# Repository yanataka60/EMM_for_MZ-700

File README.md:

# EMMボード for MZ-700

　MZ-700、MZ-80K、MZ-80C、MZ-1200、MZ-1500用の512K S-RAM EMMボードを作ってみました。

　EMMが対応しているHuBASICはMZ-700用だけです。MZ-80K用、MZ-1500用HuBASICはEMMに対応していないので外部記憶装置として使うためにはI/Oポートを直接制御して読み書きする必要があります。

　特徴としては、

　1)I/Oポートは、I・Oデータ機器 PIO-3034互換なのでそのままPIO-3034(320K EMM)として使えます。

　2)CR-2032のバックアップにより電源を切ってもメモリ内容が保持されます。(Rev1.5のバックアップ期間は計算上数年は大丈夫です。)

　3)スイッチにより書込み禁止にできます。

　4)I/Oポートから直接EMMを読み書きすれば512K外部RAMとして使えます。

　5)MZ-700_SD、MZ-80K_SD、MZ-1500_SDと併用すれば512KまるごとSDカードからLOAD、SAVEが可能です。

　6)ジャンパによりEMM0～EMM3のいずれかに設定して使えます。

　7)おまけでアドレスカウンタリセットを付けました。

#### 注)　出来ればMZ-700本体内から5Vを取り出し、EMMボードに供給してください。

#### 　　 電源アダプタを接続しての外部電源で使用する場合には次の順序で電源の入り切りを行わないとバックアップが正常に行われません。ただし、S4スイッチがROM側になっていれば電源入り切りの順番に影響されません。

#### 　　 1)電源を入れるときにはEMMボードより先にMZ-700本体の電源を入れる。

#### 　　 2)電源を切るときには先にEMMボードの電源を切ってからMZ-700本体の電源を切る。

　なお、MZ-700、MZ-80K、MZ-1500本体の通常の電源ON/OFFでの正常動作は確認していますが、電源ON/OFFを瞬間的に繰り返すような無理な使い方をするとEMMのバックアップが正常に動作しないことがあります。電源ON/OFFを瞬間的に繰り返すと電源ユニット(電源アダプタ)にもダメージが及ぶこともあるので電源ON/OFFは間をおいて行ってください。

## 回路図
[回路図](https://github.com/yanataka60/EMM_for_MZ-700/blob/main/KiCad/MZ700_EMM.pdf)

## 部品表
|番号|品名|数量|備考|
| ------------ | ------------ | ------------ | ------------ |
|C1-C14,C17|積層セラミックコンデンサ 0.1uF|15||
|C15|積層セラミックコンデンサ 220pF|1||
|C16|電解コンデンサ 100uF|1||
|D1-D2|ダイオード 1N4148|2|1S4から1N4148に変更|
|Q1|FET 2N7000|1||
|J1|コネクタ 2Pin|1|ピンヘッダで代用するときはGNDと間違えないよう1Pinで5Vだけにしたほうが良い|
|J2|DCジャック|1||
|R1|カーボン抵抗 100Ω|1||
|R2|カーボン抵抗 1k|1||
|R3|カーボン抵抗 10k|1||
|S1|3Pスライドスイッチ|1|秋月電子通商 SS12D01G4など|
|S2,S3|3Pスライドスイッチ又は1x3ピンヘッダとジャンパーピン|1|秋月電子通商 SS12D01G4又はPH-1X3SG,MJ-254-6BK等|
|S4|3Pスライドスイッチ|1|秋月電子通商 SS12D01G4など|
|U1,U15|74LS04|2|樫木総業等|
|U2|74LS14|1|樫木総業等|
|U3,U14|74LS245|2|樫木総業等|
|U4|74LS30|1|樫木総業等|
|U5-U9|74LS193|5|樫木総業等|
|U10,U11|74LS138|2|樫木総業等|
|U12|SRAM HM628512|1|注1)|
|U13|74LS11|1|樫木総業等|
|BT1|ボタン電池基板取付用ホルダー CR2032用(小型タイプ)|1|秋月電子通商 CH25-2032LFなど|

注1)DIPで設計しています。SOPを入手した場合にはこちらの変換基板を使うことで装着できます。

https://github.com/yanataka60/SOPtoDIP32

## I/Oポート
### EMM0
ジャンパピンA3、A2とも0の位置にします。

|アドレス|R/W|説明|
| ------------ | ------------ | ------------ |
|00h|R|アドレスカウンタリセット|
|00h|W|アドレスカウンタ Bit[7:0]|
|01h|W|アドレスカウンタ Bit[15:8]|
|02h|W|アドレスカウンタ Bit[18:16]|
|03h|R|データ読み出し:アドレスカウンタ+1|
|03h|W|データ書き込み:アドレスカウンタ+1|
### EMM1
ジャンパピンA3を0、A2を1の位置にします。

|アドレス|R/W|説明|
| ------------ | ------------ | ------------ |
|04h|R|アドレスカウンタリセット|
|04h|W|アドレスカウンタ Bit[7:0]|
|05h|W|アドレスカウンタ Bit[15:8]|
|06h|W|アドレスカウンタ Bit[18:16]|
|07h|R|データ読み出し:アドレスカウンタ+1|
|07h|W|データ書き込み:アドレスカウンタ+1|
### EMM2
ジャンパピンA3を1、A2を0の位置にします。

|アドレス|R/W|説明|
| ------------ | ------------ | ------------ |
|08h|R|アドレスカウンタリセット|
|08h|W|アドレスカウンタ Bit[7:0]|
|09h|W|アドレスカウンタ Bit[15:8]|
|0Ah|W|アドレスカウンタ Bit[18:16]|
|0Bh|R|データ読み出し:アドレスカウンタ+1|
|0Bh|W|データ書き込み:アドレスカウンタ+1|
### EMM3
ジャンパピンA3、A2とも1の位置にします。

|アドレス|R/W|説明|
| ------------ | ------------ | ------------ |
|0Ch|R|アドレスカウンタリセット|
|0Ch|W|アドレスカウンタ Bit[7:0]|
|0Dh|W|アドレスカウンタ Bit[15:8]|
|0Eh|W|アドレスカウンタ Bit[18:16]|
|0Fh|R|データ読み出し:アドレスカウンタ+1|
|0Fh|W|データ書き込み:アドレスカウンタ+1|

## SAMPLEプログラム
　SAMPLEフォルダ内にEMMMENU、EMMCHECK、EMMTESTを置きました。

　使い方については、フォルダ内のREADME.mdを参照してください。

## EMMからの起動
　せっかくバッテリーバックアップに対応させたのでMZ-700_SD、MZ-1500_SDからコマンド「FDE0」～「FDE3」を使うことで「EMM0」～「EMM3」のHuBASICを起動できるようにしてみました。

　MZ-700_SD、MZ-1500_SDのROMをEMM対応に書き換える必要があります。

　MZ-700_SD、MZ-1500_SDの「EMMボード for MZ-700からの起動」を参照してください。

　https://github.com/yanataka60/MZ-700_SD?tab=readme-ov-file#emm%E3%83%9C%E3%83%BC%E3%83%89-for-mz-700%E3%81%8B%E3%82%89%E3%81%AE%E8%B5%B7%E5%8B%95

　https://github.com/yanataka60/MZ-1500_SD?tab=readme-ov-file#emm%E3%83%9C%E3%83%BC%E3%83%89-for-mz-700%E3%81%8B%E3%82%89%E3%81%AE%E8%B5%B7%E5%8B%95

## 初期基板をバッテリーバックアップ対応とするには
#### 2026.2.17 Rev1.5基板ではバックアップ時間が飛躍的に増加し、ICに負荷をかけない回路となりました。バッテリーバックアップを使うなら出来ればRev1.5基板に更新してください。

　以下に示すパターンカット、ジャンパ、追加部品(抵抗10k×1本、ダイオード1S4×1本)で改造することで初期基板をバッテリーバックアップ対応とすることが可能です。

　ただし、パターンカット個所がU13 74LS11、U15 74LS04のICソケット内側にもあるのでEMMボード組み立て済みの場合にはICソケットを一旦取り外す必要があります。

### パターンカット個所
　U13 74LS11の9Pin、10Pin、11PinをGNDから切り離します。

　U15 74LS04の11Pin、13PinをGNDから切り離します。

　U12 HM628512の29PinとU11 74LS138 12Pinとの接続をカットします。

　U12 HM628512の22、24Pin、R2 10Kとの接続点とU11 74LS138 5Pinとの接続をカットします。

部品面全体
.JPG)

部品面拡大1
.JPG)

部品面拡大2
.JPG)

ハンダ面全体
.JPG)

ハンダ面拡大1
.JPG)

ハンダ面拡大2
.JPG)

ハンダ面拡大3
.JPG)

### ジャンパ個所
　U11 74LS138 5PinとU13 74LS11 11Pin

　U13 74LS11 8PinとU12 HM628512 24Pin(画像ではR2 10KのU12 HM628512 24Pinと接続されている方)

　U11 74LS138 12PinとU15 74LS04 13Pin

　U15 74LS04 12Pinと11Pin

　U15 74LS04 10Pinとダイオード 1S4 アノード

　ダイオード 1S4 カソードとU12 HM628512 29Pin

　U12 HM628512 29Pinと抵抗 10KとU12 HM628512 32Pin

ハンダ面全体

## 追記
2025.12.26 SAMPLEプログラムを追加しました。

2025.12.28 バッテリーバックアップしていてもメモリ内容が変わってしまう症状が時々発生しています。原因と対策を検討中です。

2026.1.1 簡単な修正では症状を抑えることが出来ないのでこのバージョンではバッテリーバックアップは断念し、対策を練りなおします。

2026.1.23 バッテリーバックアップ正常版(Rev1.2)に更新。初期基板をバッテリーバックアップ対応とするための改修方法を記述。

2026.1.23 バックアップ期間について追記。

2026.1.24 HM628512の書き込み時WE信号が瞬間的に5.9Vほどの電圧が掛かることを記述。すーぱーたーぼさんご指摘ありがとうございました。

2026.1.25 D1,D2を1S4から1N4148に変更。AIGOU Yoshiakiさんアドバイスありがとうございました。

2026.2.17 すーぱーたーぼさんに提案していただいていたn-FETを用いたバッテリーバックアップ回路を採用しました。すーぱーたーぼさんアドバイスありがとうございました。

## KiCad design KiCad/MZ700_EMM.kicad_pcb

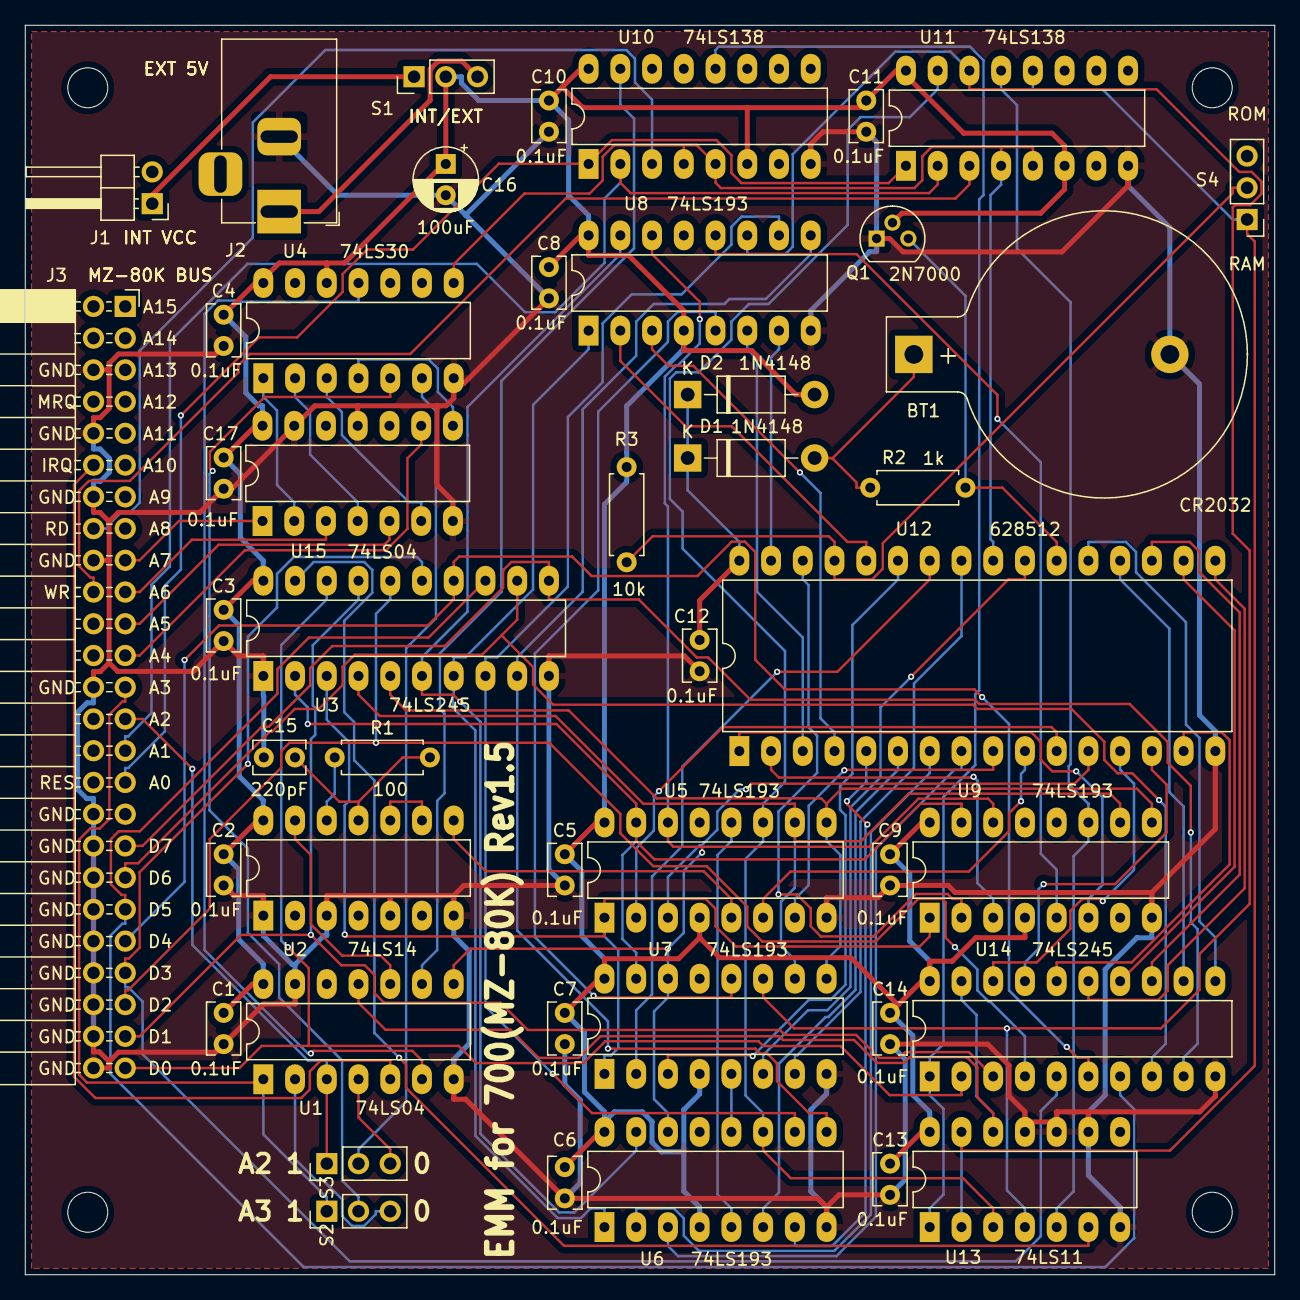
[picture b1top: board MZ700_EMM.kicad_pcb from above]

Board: 2 copper layers, 100.0 x 100.0 mm, 50 parts (0 on the bottom side), 90 nets.

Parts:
BT1: Battery_Cell; BatteryHolder_Keystone_103_1x20mm
C1, C2, C3, C4, C5, C6, C7, C8, C9, C10, C11, C12, C13, C14, C17: 0.1uF; C_Rect_L4.0mm_W2.5mm_P2.50mm
C15: 220pF; C_Rect_L4.0mm_W2.5mm_P2.50mm
C16: 100uF; CP_Radial_D5.0mm_P2.50mm
D1, D2: 1N4148; D_DO-41_SOD81_P10.16mm_Horizontal
J1: INT VCC; PinHeader_1x02_P2.54mm_Horizontal
J2: EXT 5V; BarrelJack_Horizontal
J3: MZ-80K BUS; PinSocket_2x25_P2.54mm_Horizontal
MH1, MH2, MH3, MH4: MountingHole_3.2mm_M3
Q1: 2N7000; TO-92
R1: 100; R_Axial_DIN0207_L6.3mm_D2.5mm_P7.62mm_Horizontal
R2: 1k; R_Axial_DIN0207_L6.3mm_D2.5mm_P7.62mm_Horizontal
R3: 10k; R_Axial_DIN0207_L6.3mm_D2.5mm_P7.62mm_Horizontal
S1: INT/EXT; PinHeader_1x03_P2.54mm_Vertical
S2: A3_select; PinHeader_1x03_P2.54mm_Vertical
S3: A2_select; PinHeader_1x03_P2.54mm_Vertical
S4: SLIDE_SWITCH_3P; PinHeader_1x03_P2.54mm_Vertical
U1, U15: 74LS04; DIP-14_W7.62mm_LongPads
U2: 74LS14; DIP-14_W7.62mm_LongPads
U3, U14: 74LS245; DIP-20_W7.62mm_LongPads
U4: 74LS30; DIP-14_W7.62mm_LongPads
U5, U6, U7, U8, U9: 74LS193; DIP-16_W7.62mm_LongPads
U10, U11: 74LS138; DIP-16_W7.62mm_LongPads
U12: HM628512LFP-5; DIP-32_W15.24mm_LongPads
U13: 74LS11; DIP-14_W7.62mm_LongPads

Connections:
+5V: C1.1, C2.1, C3.1, C4.1, C5.1, C6.1, C7.1, C8.1, C9.1, C10.1, C11.1, C13.1, C14.1, C16.1, C17.1, D2.2, Q1.2, R3.2, S1.2, U1.14, U2.14, U3.20, U4.12, U4.14, U5.4, U5.16, U6.4, U6.16, U7.4, U7.16, U8.4, U8.16, U9.4, U9.16, U10.6, U10.16, U11.6, U11.16, U13.14, U14.20, U15.14
/A0: J3.31, U10.1, U11.1
/A1: J3.29, U10.2, U11.2
/A2: J3.27, S3.1, U1.3
/A3: J3.25, S2.1, U1.1
/A4: J3.23, U15.9
/A5: J3.21, U15.5
/A6: J3.19, U15.3
/A7: J3.17, U15.1
/D0: J3.49, U3.18, U14.2
/D1: J3.47, U3.17, U14.3
/D2: J3.45, U3.16, U14.4
/D3: J3.43, U3.15, U14.5
/D4: J3.41, U3.14, U14.6
/D5: J3.39, U3.13, U14.7
/D6: J3.37, U3.12, U14.8
/D7: J3.35, U3.11, U14.9
/x0_RD: U1.9, U10.15
/x0_WR: U5.11, U6.11, U11.15, U13.3
/x1_WR: U7.11, U8.11, U11.14, U13.4
/x2_WR: U9.11, U11.13, U13.5
/x3_RD: U10.12, U13.1, U14.1
/x3_WR: S4.1, U11.12, U13.2, U13.13
/~IORQ: J3.12, U1.5
/~RD: J3.16, U10.3
/~WR: J3.20, U11.3
GND: BT1.2, C1.2, C2.2, C3.2, C4.2, C5.2, C6.2, C7.2, C8.2, C9.2, C10.2, C11.2, C12.2, C13.2, C14.2, C15.2, C16.2, C17.2, J2.2, J3.6, J3.10, J3.14, J3.18, J3.26, J3.34, J3.36, J3.38, J3.40, J3.42, J3.44, J3.46, J3.48, J3.50, Q1.1, U1.7, U1.13, U2.1, U2.3, U2.5, U2.7, U3.1, U3.10, U4.7, U5.8, U6.8, U7.8, U8.8, U9.8, U10.8, U11.8, U12.16, U13.7, U13.9, U13.10, U13.11, U14.10, U15.7, U15.11, U15.13
unnamed: BT1.1, D1.2, R2.2
unnamed: C12.1, D1.1, D2.1, U12.32
unnamed: C15.1, R1.2, U2.11
unnamed: J1.1, S1.1
unnamed: J2.1, S1.3
unnamed: Q1.3, R2.1, U12.22
unnamed: R1.1, U2.12
unnamed: R3.1, S4.2, U12.29
unnamed: S2.2, U4.5
unnamed: S2.3, U1.2
unnamed: S3.2, U4.6
unnamed: S3.3, U1.4
unnamed: U1.6, U4.11
unnamed: U1.8, U5.14, U6.14, U7.14, U8.14, U9.14
unnamed: U1.10, U2.13
unnamed: U1.11, U13.12, U14.19
unnamed: U2.8, U5.5
unnamed: U2.9, U2.10
unnamed: U3.2, U5.15, U7.15, U9.15
unnamed: U3.3, U5.1, U7.1, U9.1
unnamed: U3.4, U5.10, U7.10, U9.10
unnamed: U3.5, U5.9, U7.9, U9.9
unnamed: U3.6, U6.15, U8.15
unnamed: U3.7, U6.1, U8.1
unnamed: U3.8, U6.10, U8.10
unnamed: U3.9, U6.9, U8.9
unnamed: U5.12, U6.5
unnamed: U6.12, U7.5
unnamed: U7.12, U8.5
unnamed: U8.12, U9.5
unnamed: U4.8, U10.4, U10.5, U11.4, U11.5, U12.24
unnamed: U9.6, U12.1
unnamed: U9.3, U12.2
unnamed: U8.6, U12.3
unnamed: U8.3, U12.4
unnamed: U6.7, U12.5
unnamed: U6.6, U12.6
unnamed: U6.2, U12.7
unnamed: U6.3, U12.8
unnamed: U5.7, U12.9
unnamed: U5.6, U12.10
unnamed: U5.2, U12.11
unnamed: U5.3, U12.12
unnamed: U12.13, U14.18
unnamed: U12.14, U14.17
unnamed: U12.15, U14.16
unnamed: U12.17, U14.15
unnamed: U12.18, U14.14
unnamed: U12.19, U14.13
unnamed: U12.20, U14.12
unnamed: U12.21, U14.11
unnamed: U7.6, U12.23
unnamed: U7.7, U12.25
unnamed: U7.2, U12.26
unnamed: U7.3, U12.27
unnamed: U8.2, U12.28
unnamed: U9.2, U12.30
unnamed: U8.7, U12.31
unnamed: U3.19, U13.6
unnamed: U4.1, U15.2
unnamed: U4.2, U15.4
unnamed: U4.3, U15.6
unnamed: U4.4, U15.8
